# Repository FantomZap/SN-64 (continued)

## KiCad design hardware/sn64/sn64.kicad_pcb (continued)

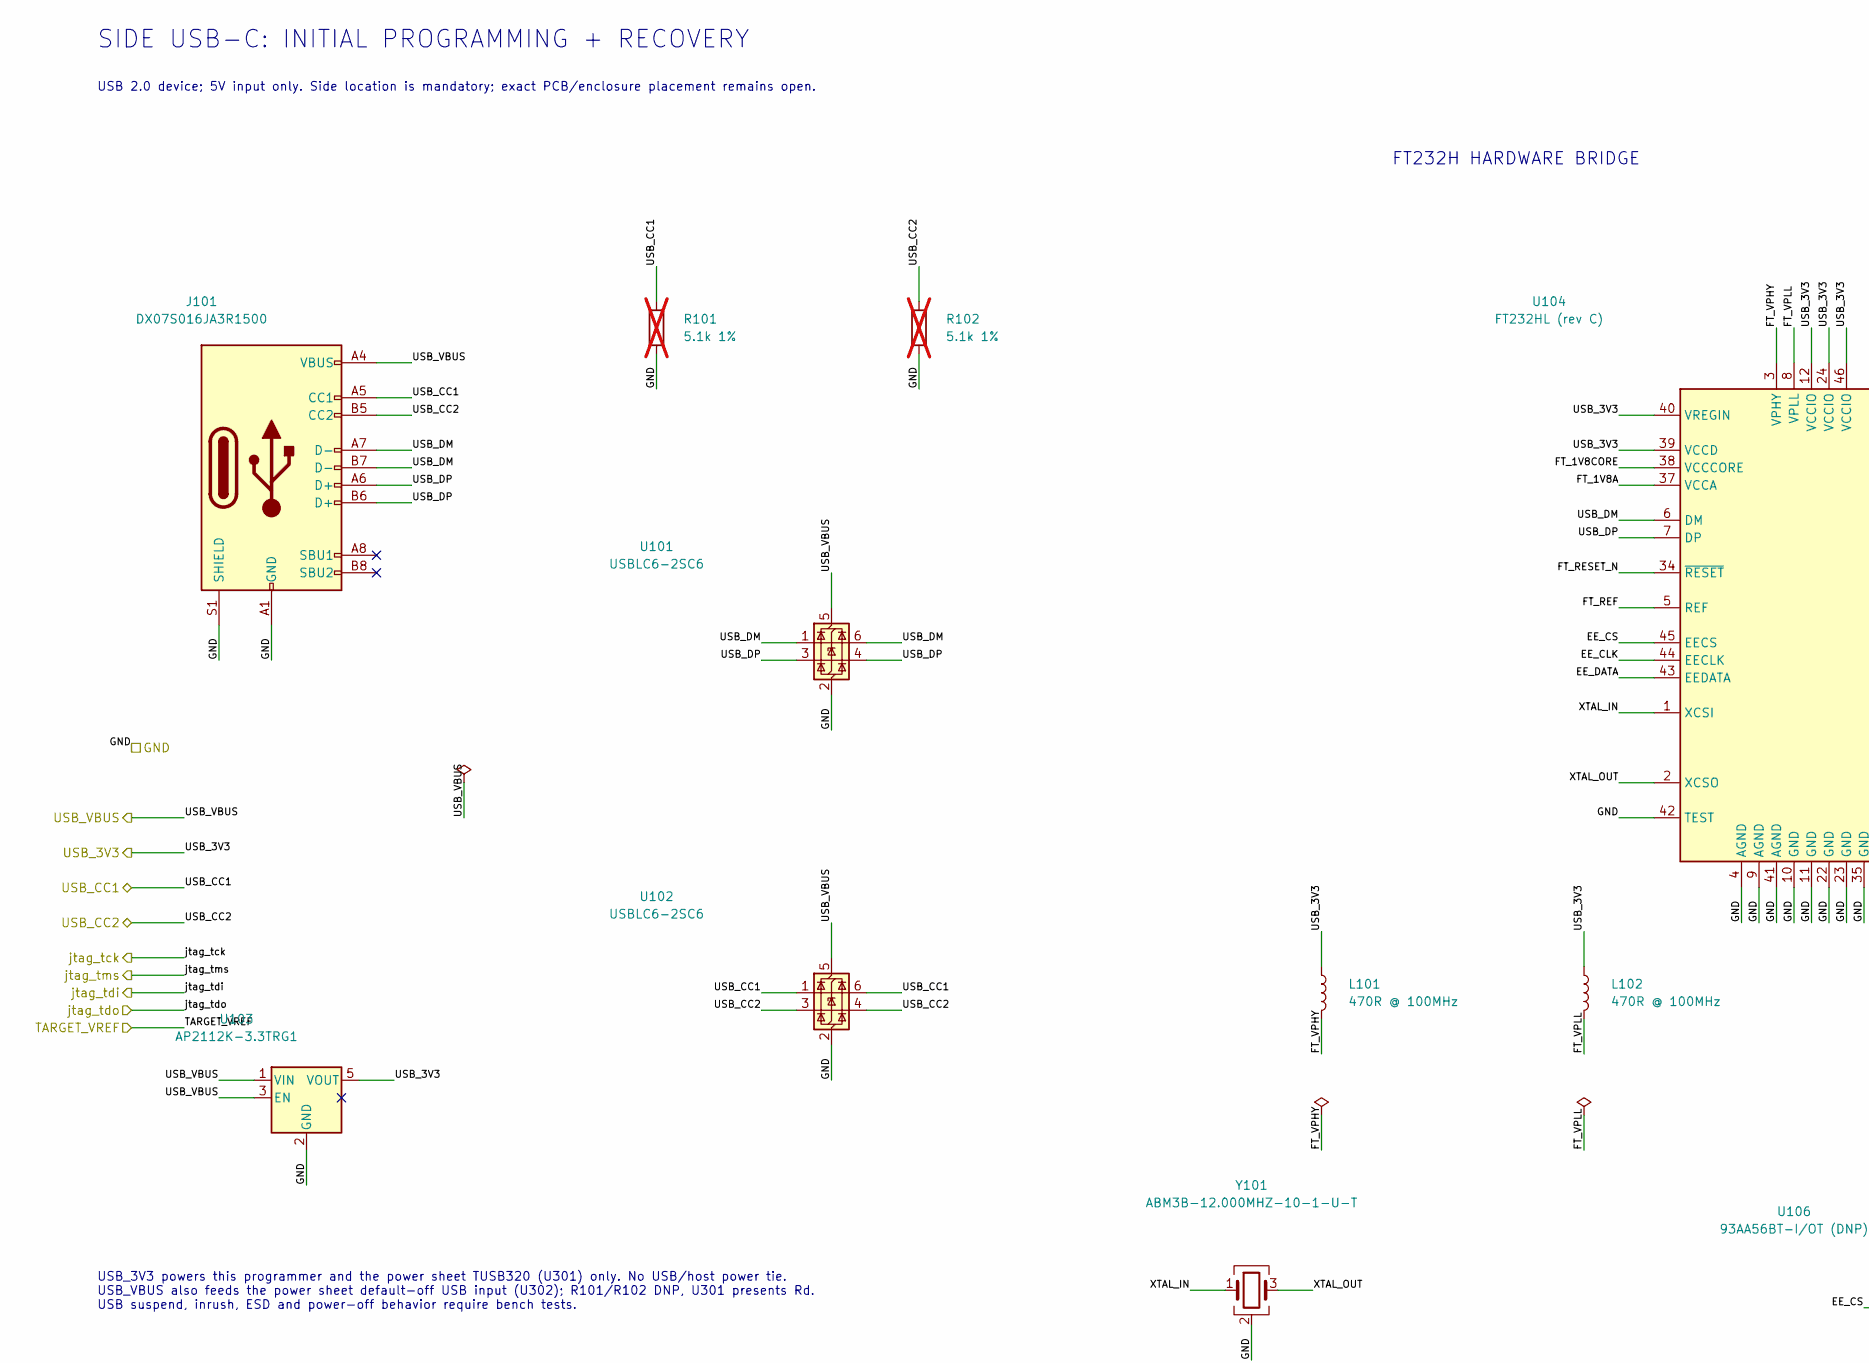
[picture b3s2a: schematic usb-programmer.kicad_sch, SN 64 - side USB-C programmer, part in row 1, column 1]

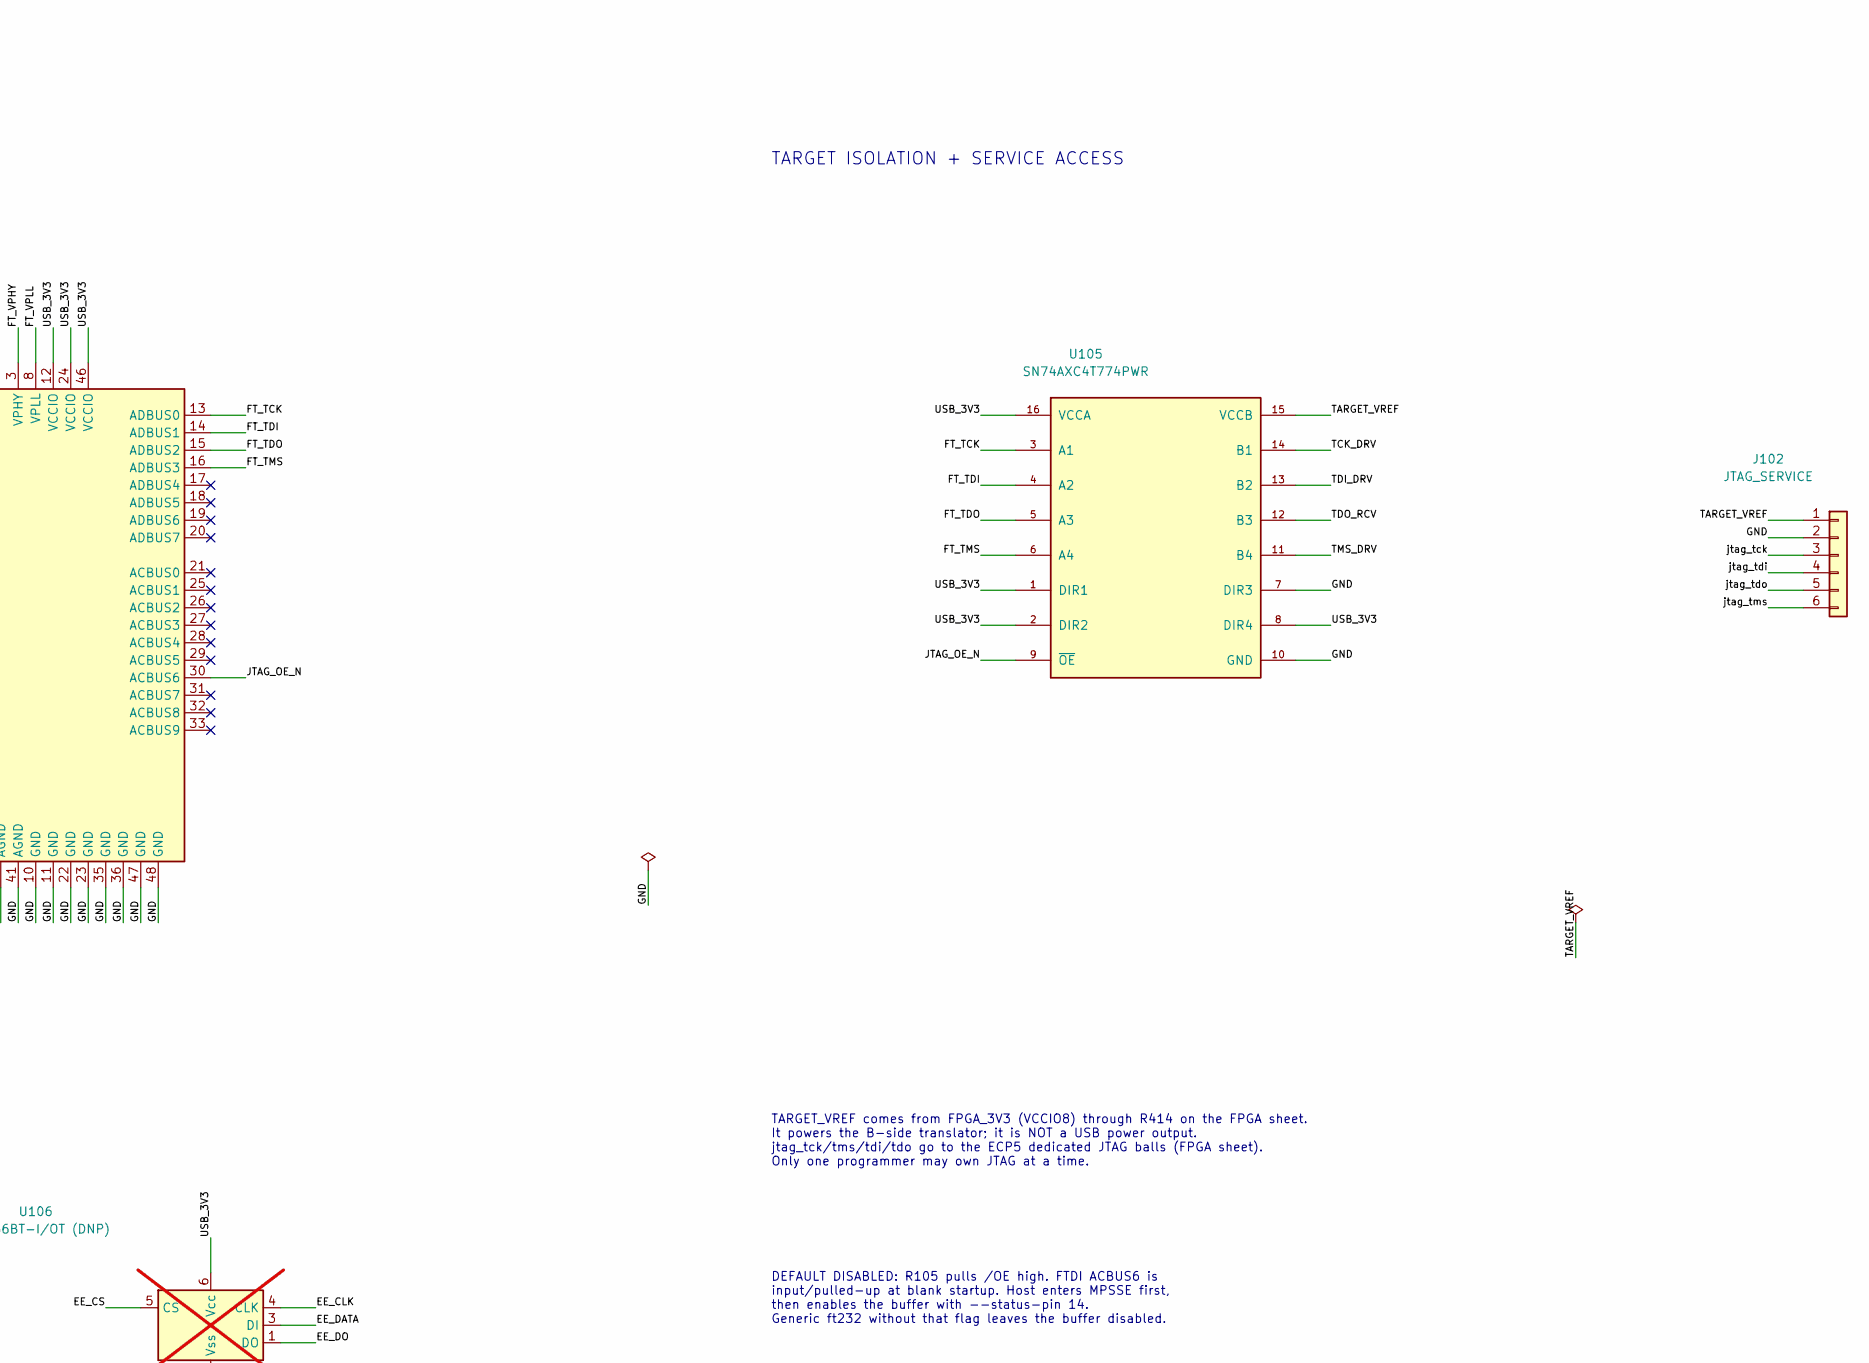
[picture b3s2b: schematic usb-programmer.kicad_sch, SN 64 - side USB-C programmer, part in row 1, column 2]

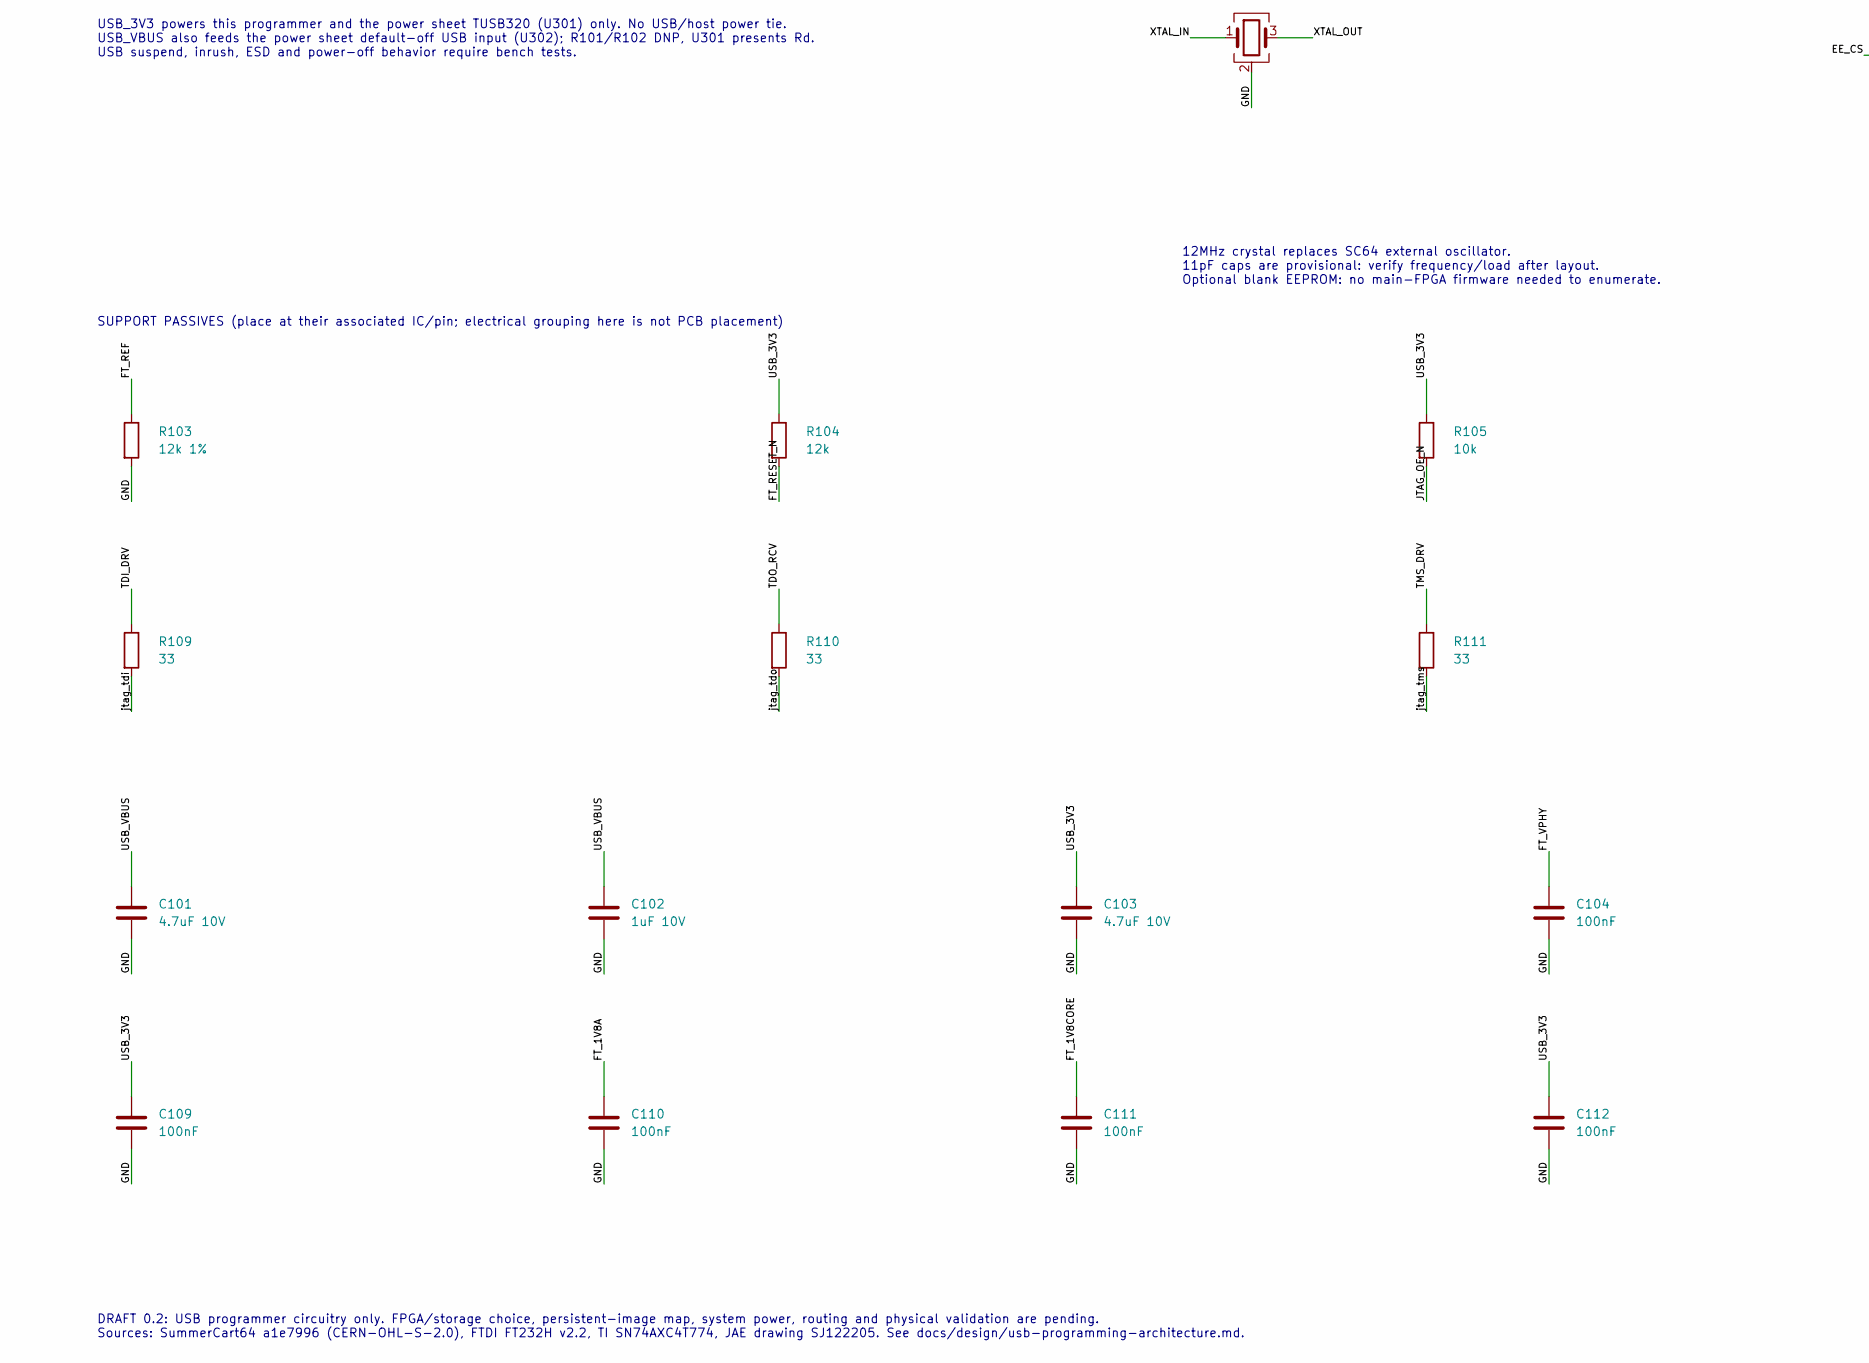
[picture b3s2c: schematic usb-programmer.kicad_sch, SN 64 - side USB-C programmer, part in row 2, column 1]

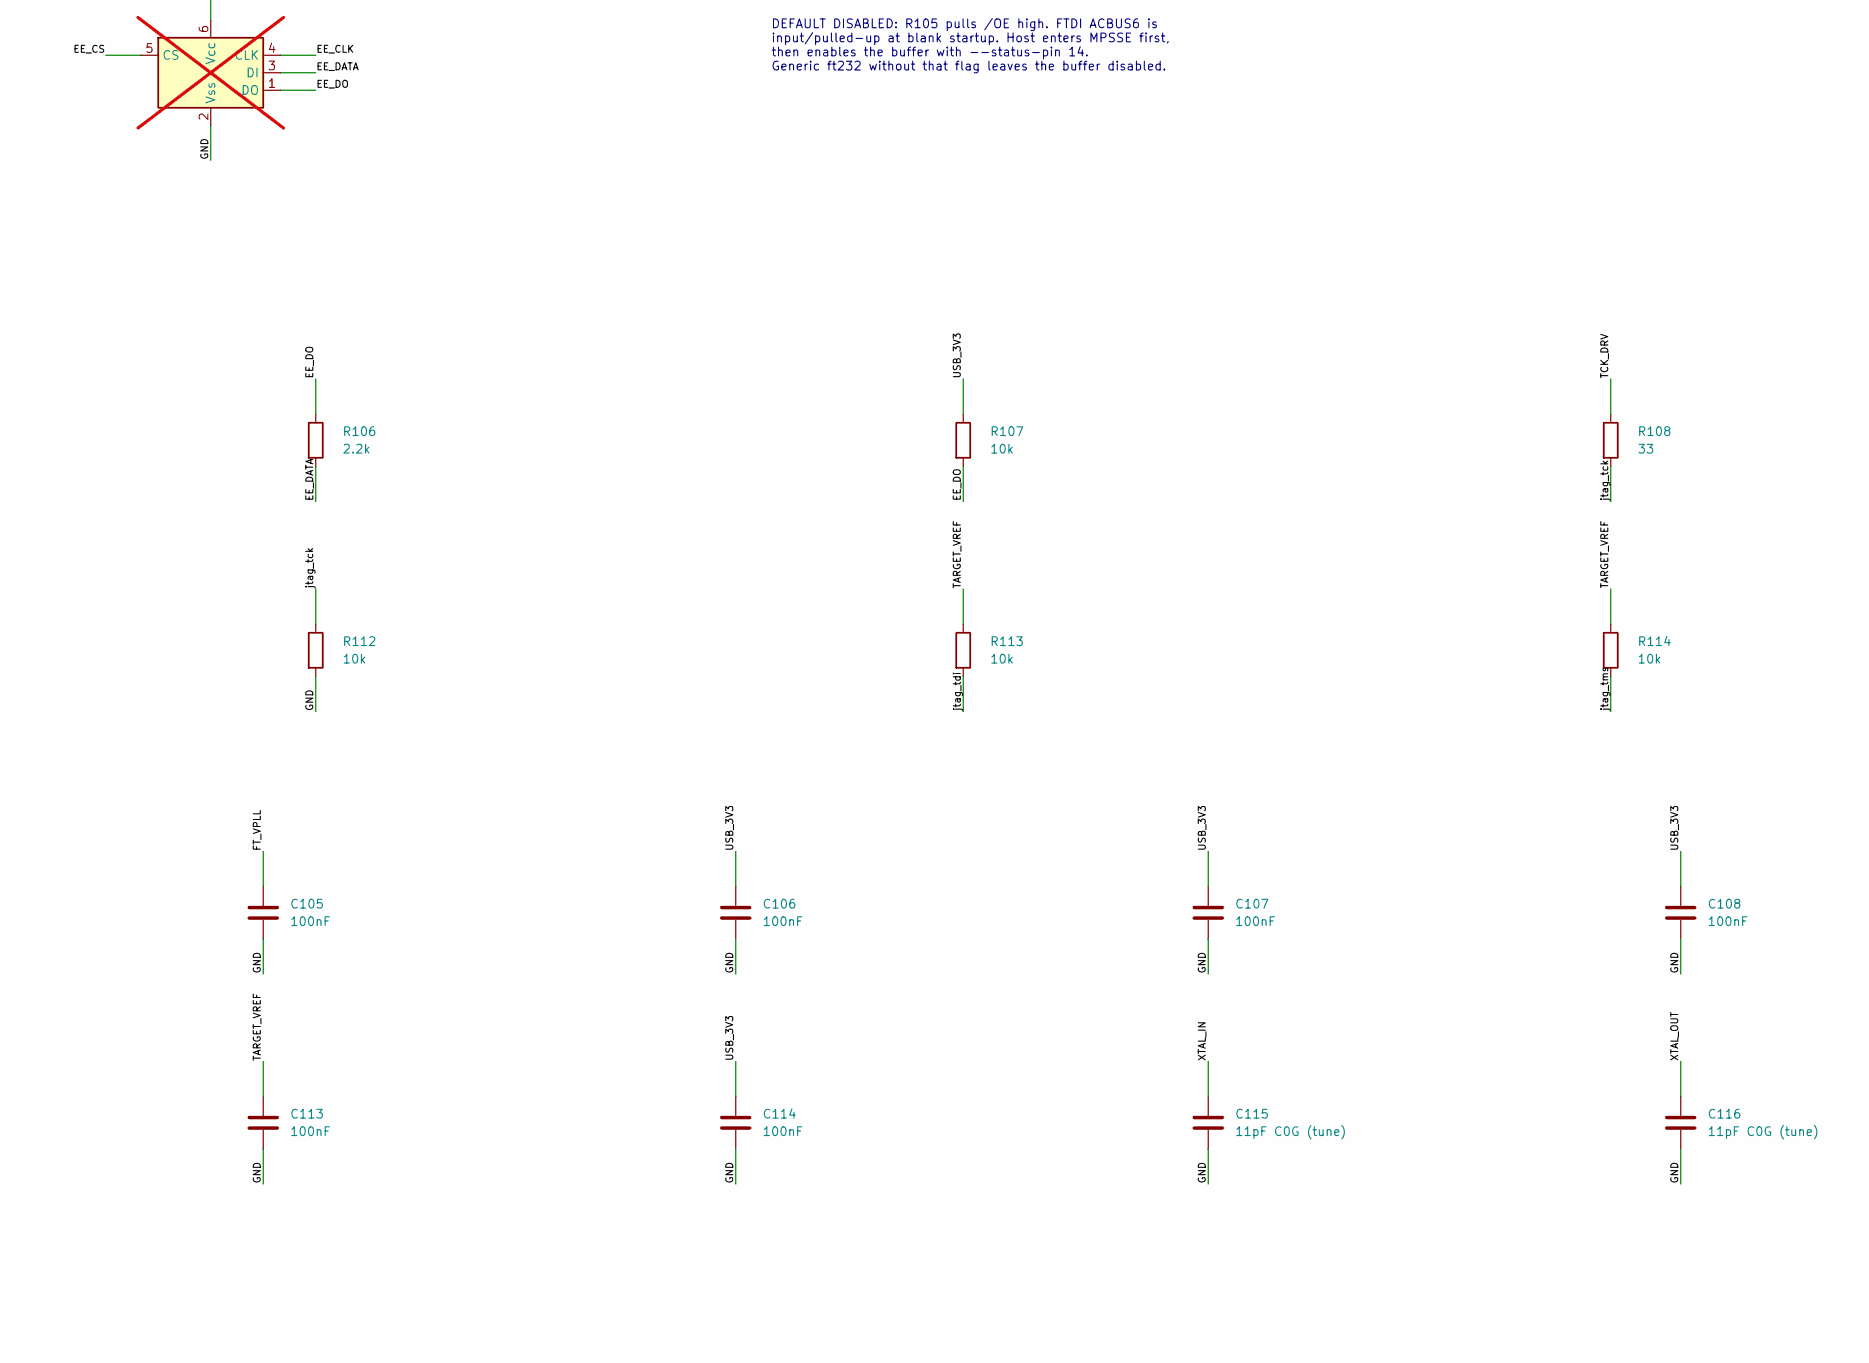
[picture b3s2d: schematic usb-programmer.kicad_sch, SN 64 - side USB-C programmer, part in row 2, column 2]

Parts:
C101, C103: 4.7uF 10V; C_0603_1608Metric
C102: 1uF 10V; C_0603_1608Metric
C104, C105, C106, C107, C108, C109, C110, C111, C112, C113, C114: 100nF; C_0603_1608Metric
C115, C116: 11pF C0G (tune); C_0603_1608Metric
J101: DX07S016JA3R1500; USB_C_JAE_DX07S016JA3R1500
J102: JTAG_SERVICE; PinHeader_1x06_P2.54mm_Vertical
L101, L102: 470R @ 100MHz; L_0603_1608Metric
R101, R102: 5.1k 1%; R_0603_1608Metric; not fitted
R103: 12k 1%; R_0603_1608Metric
R104: 12k; R_0603_1608Metric
R105, R107, R112, R113, R114: 10k; R_0603_1608Metric
R106: 2.2k; R_0603_1608Metric
R108, R109, R110, R111: 33; R_0603_1608Metric
U101, U102: USBLC6-2SC6; SOT-23-6
U103: AP2112K-3.3TRG1; SOT-23-5
U104: FT232HL (rev C); LQFP-48_7x7mm_P0.5mm
U105: SN74AXC4T774PWR; TSSOP-16_4.4x5mm_P0.65mm
U106: 93AA56BT-I/OT (DNP); SOT-23-6; not fitted
Y101: ABM3B-12.000MHZ-10-1-U-T; Crystal_SMD_Abracon_ABM3B-4Pin_5.0x3.2mm

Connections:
/GND: C101.2, C102.2, C103.2, C104.2, C105.2, C106.2, C107.2, C108.2, C109.2, C110.2, C111.2, C112.2, C113.2, C114.2, C115.2, C116.2, J101.A1 (GND), J101.A12 (GND), J101.B1 (GND), J101.B12 (GND), J101.S1 (SHIELD), J102.2, R101.2, R102.2, R103.2, R112.2, U101.2 (GND), U102.2 (GND), U103.2 (GND), U104.4 (AGND), U104.9 (AGND), U104.10 (GND), U104.11 (GND), U104.22 (GND), U104.23 (GND), U104.35 (GND), U104.36 (GND), U104.41 (AGND), U104.42 (TEST), U104.47 (GND), U104.48 (GND), U105.7 (DIR3), U105.10 (GND), U106.2 (Vss), Y101.2 (G), Y101.4 (G); also elsewhere on the board
/TARGET_VREF: C113.1, J102.1, R113.1, R114.1, U105.15 (VCCB); also elsewhere on the board
/USB-C programmer/EE_CLK: U104.44 (EECLK), U106.4 (CLK)
/USB-C programmer/EE_CS: U104.45 (EECS), U106.5 (CS)
/USB-C programmer/EE_DATA: R106.2, U104.43 (EEDATA), U106.3 (DI)
/USB-C programmer/EE_DO: R106.1, R107.2, U106.1 (DO)
/USB-C programmer/FT_1V8A: C110.1, U104.37 (VCCA)
/USB-C programmer/FT_1V8CORE: C111.1, U104.38 (VCCCORE)
/USB-C programmer/FT_REF: R103.1, U104.5 (REF)
/USB-C programmer/FT_RESET_N: R104.2, U104.34 (~RESET)
/USB-C programmer/FT_TCK: U104.13 (ADBUS0), U105.3 (A1)
/USB-C programmer/FT_TDI: U104.14 (ADBUS1), U105.4 (A2)
/USB-C programmer/FT_TDO: U104.15 (ADBUS2), U105.5 (A3)
/USB-C programmer/FT_TMS: U104.16 (ADBUS3), U105.6 (A4)
/USB-C programmer/FT_VPHY: C104.1, L101.2, U104.3 (VPHY)
/USB-C programmer/FT_VPLL: C105.1, L102.2, U104.8 (VPLL)
/USB-C programmer/JTAG_OE_N: R105.2, U104.30 (ACBUS6), U105.9 (~OE)
/USB-C programmer/TCK_DRV: R108.1, U105.14 (B1)
/USB-C programmer/TDI_DRV: R109.1, U105.13 (B2)
/USB-C programmer/TDO_RCV: R110.1, U105.12 (B3)
/USB-C programmer/TMS_DRV: R111.1, U105.11 (B4)
/USB-C programmer/USB_DM: J101.A7 (D-), J101.B7 (D-), U101.1 (I/O1), U101.6 (I/O1), U104.6 (DM)
/USB-C programmer/USB_DP: J101.A6 (D+), J101.B6 (D+), U101.3 (I/O2), U101.4 (I/O2), U104.7 (DP)
/USB-C programmer/XTAL_IN: C115.1, U104.1 (XCSI), Y101.1
/USB-C programmer/XTAL_OUT: C116.1, U104.2 (XCSO), Y101.3
/USB_3V3: C103.1, C106.1, C107.1, C108.1, C109.1, C112.1, C114.1, L101.1, L102.1, R104.1, R105.1, R107.1, U103.5 (VOUT), U104.12 (VCCIO), U104.24 (VCCIO), U104.39 (VCCD), U104.40 (VREGIN), U104.46 (VCCIO), U105.1 (DIR1), U105.2 (DIR2), U105.8 (DIR4), U105.16 (VCCA), U106.6 (Vсс); also elsewhere on the board
/USB_CC1: J101.A5 (CC1), R101.1, U102.1 (I/O1), U102.6 (I/O1); also elsewhere on the board
/USB_CC2: J101.B5 (CC2), R102.1, U102.3 (I/O2), U102.4 (I/O2); also elsewhere on the board
/USB_VBUS: C101.1, C102.1, J101.A4 (VBUS), J101.A9 (VBUS), J101.B4 (VBUS), J101.B9 (VBUS), U101.5 (VBUS), U102.5 (VBUS), U103.1 (VIN), U103.3 (EN); also elsewhere on the board
/jtag_tck: J102.3, R108.2, R112.1; also elsewhere on the board
/jtag_tdi: J102.4, R109.2, R113.2; also elsewhere on the board
/jtag_tdo: J102.5, R110.2; also elsewhere on the board
/jtag_tms: J102.6, R111.2, R114.2; also elsewhere on the board

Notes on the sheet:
SIDE USB-C: INITIAL PROGRAMMING + RECOVERY
USB 2.0 device; 5V input only. Side location is mandatory; exact PCB/enclosure placement remains open.
FT232H HARDWARE BRIDGE
TARGET ISOLATION + SERVICE ACCESS
TARGET_VREF comes from FPGA_3V3 (VCCIO8) through R414 on the FPGA sheet. It powers the B-side translator; it is NOT a USB power output. jtag_tck/tms/tdi/tdo go to the ECP5 dedicated JTAG balls (FPGA sheet). Only one programmer may own JTAG at a time.
DEFAULT DISABLED: R105 pulls /OE high. FTDI ACBUS6 is input/pulled-up at blank startup. Host enters MPSSE first, then enables the buffer with --status-pin 14. Generic ft232 without that flag leaves the buffer disabled.
USB_3V3 powers this programmer and the power sheet TUSB320 (U301) only. No USB/host power tie. USB_VBUS also feeds the power sheet default-off USB input (U302); R101/R102 DNP, U301 presents Rd. USB suspend, inrush, ESD and power-off behavior require bench tests.
12MHz crystal replaces SC64 external oscillator. 11pF caps are provisional: verify frequency/load after layout. Optional blank EEPROM: no main-FPGA firmware needed to enumerate.
SUPPORT PASSIVES (place at their associated IC/pin; electrical grouping here is not PCB placement)
DRAFT 0.2: USB programmer circuitry only. FPGA/storage choice, persistent-image map, system power, routing and physical validation are pending. Sources: SummerCart64 a1e7996 (CERN-OHL-S-2.0), FTDI FT232H v2.2, TI SN74AXC4T774, JAE drawing SJ122205. See docs/design/usb-programming-architecture.md.

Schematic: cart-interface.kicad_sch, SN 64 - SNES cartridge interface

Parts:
C201, C202, C203, C204, C205, C206, C207, C208, C209, C210, C211, C212, C213, C214, C215, C216, C217, C218, C219, C220, C221, C222, C223, C224, C225, C226, C227, C228, C229, C230, C231: 100nF; C_0603_1608Metric
C232, C233: 10uF 10V; C_0805_2012Metric
Q201: 2N7002; SOT-23
R201, R202: 2.2k; R_0603_1608Metric
R203, R204: 1k; R_0603_1608Metric
R205, R218, R219: 100k; R_0603_1608Metric
R206, R207, R208: 4.7k; R_0603_1608Metric
R209, R210, R211, R212, R213, R216, R217, R220, R221: 10k; R_0603_1608Metric
R214, R215: 33; R_0603_1608Metric
RN201, RN202, RN203, RN204, RN205, RN206, RN207, RN208, RN209, RN210, RN211, RN212, RN213: 33 (4x0603, tune); R_Array_Convex_4x0603
TP201: AUDIO_L; TestPoint_Pad_D1.0mm
TP202: AUDIO_R; TestPoint_Pad_D1.0mm
U201, U202, U203, U204, U205, U206, U207: SN74LVC4245APWR; TSSOP-24_4.4x7.8mm_P0.65mm
U209: SN74LVC244APWR; TSSOP-20_4.4x6.5mm_P0.65mm
U210, U211, U212: SN74LVC1G07DBVR; SOT-23-5
U213, U214: SN74LVC1G06DBVR; SOT-23-5
U215, U216: SN74LVC1T45DBVR; SOT-23-6; LCSC C7843

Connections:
/GND: C201.2, C202.2, C203.2, C204.2, C205.2, C206.2, C207.2, C208.2, C209.2, C210.2, C211.2, C212.2, C213.2, C214.2, C215.2, C216.2, C217.2, C218.2, C219.2, C220.2, C221.2, C222.2, C223.2, C224.2, C225.2, C226.2, C227.2, C228.2, C229.2, C230.2, C231.2, C232.2, C233.2, Q201.2 (S), R209.2, R210.2, R216.2, R217.2, R218.2, R219.2, R220.2, R221.2, U201.2 (DIR), U201.11 (GND), U201.12 (GND), U201.13 (GND), U202.2 (DIR), U202.11 (GND), U202.12 (GND), U202.13 (GND), U203.2 (DIR), U203.11 (GND), U203.12 (GND), U203.13 (GND), U204.2 (DIR), U204.11 (GND), U204.12 (GND), U204.13 (GND), U205.2 (DIR), U205.11 (GND), U205.12 (GND), U205.13 (GND), U206.2 (DIR), U206.11 (GND), U206.12 (GND), U206.13 (GND), U206.14 (B8), U206.15 (B7), U206.16 (B6), U206.17 (B5), U206.18 (B4), U207.11 (GND), U207.12 (GND), U207.13 (GND), U209.1 (~1OE), U209.8 (1A4), U209.10 (GND), U209.11 (2A1), U209.13 (2A2), U209.15 (2A3), U209.17 (2A4), U209.19 (~2OE), U210.3 (GND), U211.3 (GND), U212.3 (GND), U213.3 (GND), U214.3 (GND), U215.2 (GND), U216.2 (GND); also elsewhere on the board
/INTERFACE_3V3: C202.1, C203.1, C205.1, C206.1, C208.1, C209.1, C211.1, C212.1, C214.1, C215.1, C217.1, C218.1, C220.1, C221.1, C222.1, C223.1, C224.1, C225.1, C226.1, C227.1, C228.1, C230.1, C233.1, R206.1, R207.1, R208.1, U201.23 (VCCB), U201.24 (VCCB), U202.23 (VCCB), U202.24 (VCCB), U203.23 (VCCB), U203.24 (VCCB), U204.23 (VCCB), U204.24 (VCCB), U205.23 (VCCB), U205.24 (VCCB), U206.23 (VCCB), U206.24 (VCCB), U207.23 (VCCB), U207.24 (VCCB), U209.20 (VCC), U210.5 (VCC), U211.5 (VCC), U212.5 (VCC), U213.5 (VCC), U214.5 (VCC), U215.1 (VCCA), U216.1 (VCCA); also elsewhere on the board
/SNES cartridge interface/CIC_OE_N_5V: R202.2, U206.22 (~OE), U211.4
/SNES cartridge interface/CTL_OE_N_5V: R201.2, U201.22 (~OE), U202.22 (~OE), U203.22 (~OE), U204.22 (~OE), U205.22 (~OE), U210.4
/SNES cartridge interface/DATA_DIR_5V: R204.2, U207.2 (DIR), U213.4
/SNES cartridge interface/DATA_OE_N_5V: R203.2, U207.22 (~OE), U212.4
/SNES cartridge interface/RESET_GATE_5V: Q201.1 (G), R205.2, U214.4
/SNES cartridge interface/XA_A0: RN201.1 (R1.1), U201.3 (A1)
/SNES cartridge interface/XA_A1: RN201.2 (R2.1), U201.4 (A2)
/SNES cartridge interface/XA_A2: RN201.3 (R3.1), U201.5 (A3)
/SNES cartridge interface/XA_A3: RN201.4 (R4.1), U201.6 (A4)
/SNES cartridge interface/XA_A4: RN202.1 (R1.1), U201.7 (A5)
/SNES cartridge interface/XA_A5: RN202.2 (R2.1), U201.8 (A6)
/SNES cartridge interface/XA_A6: RN202.3 (R3.1), U201.9 (A7)
/SNES cartridge interface/XA_A7: RN202.4 (R4.1), U201.10 (A8)
/SNES cartridge interface/XA_A8: RN203.1 (R1.1), U202.3 (A1)
/SNES cartridge interface/XA_A9: RN203.2 (R2.1), U202.4 (A2)
/SNES cartridge interface/XA_A10: RN203.3 (R3.1), U202.5 (A3)
/SNES cartridge interface/XA_A11: RN203.4 (R4.1), U202.6 (A4)
/SNES cartridge interface/XA_A12: RN204.1 (R1.1), U202.7 (A5)
/SNES cartridge interface/XA_A13: RN204.2 (R2.1), U202.8 (A6)
/SNES cartridge interface/XA_A14: RN204.3 (R3.1), U202.9 (A7)
/SNES cartridge interface/XA_A15: RN204.4 (R4.1), U202.10 (A8)
/SNES cartridge interface/XA_A16: RN205.1 (R1.1), U203.3 (A1)
/SNES cartridge interface/XA_A17: RN205.2 (R2.1), U203.4 (A2)
/SNES cartridge interface/XA_A18: RN205.3 (R3.1), U203.5 (A3)
/SNES cartridge interface/XA_A19: RN205.4 (R4.1), U203.6 (A4)
/SNES cartridge interface/XA_A20: RN206.1 (R1.1), U203.7 (A5)
/SNES cartridge interface/XA_A21: RN206.2 (R2.1), U203.8 (A6)
/SNES cartridge interface/XA_A22: RN206.3 (R3.1), U203.9 (A7)
/SNES cartridge interface/XA_A23: RN206.4 (R4.1), U203.10 (A8)
/SNES cartridge interface/XA_CIC_CLK: RN211.2 (R2.1), U206.4 (A2)
/SNES cartridge interface/XA_CIC_SLAVE_RESET: RN211.3 (R3.1), U206.5 (A3)
/SNES cartridge interface/XA_D0: RN212.1 (R1.1), U207.3 (A1)
/SNES cartridge interface/XA_D1: RN212.2 (R2.1), U207.4 (A2)
/SNES cartridge interface/XA_D2: RN212.3 (R3.1), U207.5 (A3)
/SNES cartridge interface/XA_D3: RN212.4 (R4.1), U207.6 (A4)
/SNES cartridge interface/XA_D4: RN213.1 (R1.1), U207.7 (A5)
/SNES cartridge interface/XA_D5: RN213.2 (R2.1), U207.8 (A6)
/SNES cartridge interface/XA_D6: RN213.3 (R3.1), U207.9 (A7)
/SNES cartridge interface/XA_D7: RN213.4 (R4.1), U207.10 (A8)
/SNES cartridge interface/XA_PA0: RN207.1 (R1.1), U204.3 (A1)
/SNES cartridge interface/XA_PA1: RN207.2 (R2.1), U204.4 (A2)
/SNES cartridge interface/XA_PA2: RN207.3 (R3.1), U204.5 (A3)
/SNES cartridge interface/XA_PA3: RN207.4 (R4.1), U204.6 (A4)
/SNES cartridge interface/XA_PA4: RN208.1 (R1.1), U204.7 (A5)
/SNES cartridge interface/XA_PA5: RN208.2 (R2.1), U204.8 (A6)
/SNES cartridge interface/XA_PA6: RN208.3 (R3.1), U204.9 (A7)
/SNES cartridge interface/XA_PA7: RN208.4 (R4.1), U204.10 (A8)
/SNES cartridge interface/XA_PHI2: RN210.4 (R4.1), U205.10 (A8)
/SNES cartridge interface/XA_PRD_N: RN209.3 (R3.1), U205.5 (A3)
/SNES cartridge interface/XA_PWR_N: RN209.4 (R4.1), U205.6 (A4)
/SNES cartridge interface/XA_RD_N: RN209.1 (R1.1), U205.3 (A1)
/SNES cartridge interface/XA_REFRESH: RN210.3 (R3.1), U205.9 (A7)
/SNES cartridge interface/XA_ROMSEL_N: RN210.1 (R1.1), U205.7 (A5)
/SNES cartridge interface/XA_SYSTEM_CLK: RN211.1 (R1.1), U206.3 (A1)
/SNES cartridge interface/XA_WRAMSEL_N: RN210.2 (R2.1), U205.8 (A6)
/SNES cartridge interface/XA_WR_N: RN209.2 (R2.1), U205.4 (A2)
/SNES cartridge interface/XB_CIC_DATA0: R214.1, U215.4 (B)
/SNES cartridge interface/XB_CIC_DATA1: R215.1, U216.4 (B)
/SNES_5V_CART: C201.1, C204.1, C207.1, C210.1, C213.1, C216.1, C219.1, C229.1, C231.1, C232.1, R201.1, R202.1, R203.1, R204.1, R205.1, R211.1, R212.1, R213.1, U201.1 (VCCA), U202.1 (VCCA), U203.1 (VCCA), U204.1 (VCCA), U205.1 (VCCA), U206.1 (VCCA), U207.1 (VCCA), U215.6 (VCCB), U216.6 (VCCB); also elsewhere on the board
/SNES_A0: RN201.8 (R1.2); also elsewhere on the board
/SNES_A1: RN201.7 (R2.2); also elsewhere on the board
/SNES_A2: RN201.6 (R3.2); also elsewhere on the board
/SNES_A3: RN201.5 (R4.2); also elsewhere on the board
/SNES_A4: RN202.8 (R1.2); also elsewhere on the board
/SNES_A5: RN202.7 (R2.2); also elsewhere on the board
/SNES_A6: RN202.6 (R3.2); also elsewhere on the board
/SNES_A7: RN202.5 (R4.2); also elsewhere on the board
/SNES_A8: RN203.8 (R1.2); also elsewhere on the board
/SNES_A9: RN203.7 (R2.2); also elsewhere on the board
/SNES_A10: RN203.6 (R3.2); also elsewhere on the board
/SNES_A11: RN203.5 (R4.2); also elsewhere on the board
/SNES_A12: RN204.8 (R1.2); also elsewhere on the board
/SNES_A13: RN204.7 (R2.2); also elsewhere on the board
/SNES_A14: RN204.6 (R3.2); also elsewhere on the board
/SNES_A15: RN204.5 (R4.2); also elsewhere on the board
/SNES_A16: RN205.8 (R1.2); also elsewhere on the board
/SNES_A17: RN205.7 (R2.2); also elsewhere on the board
/SNES_A18: RN205.6 (R3.2); also elsewhere on the board
/SNES_A19: RN205.5 (R4.2); also elsewhere on the board
/SNES_A20: RN206.8 (R1.2); also elsewhere on the board
/SNES_A21: RN206.7 (R2.2); also elsewhere on the board
/SNES_A22: RN206.6 (R3.2); also elsewhere on the board
/SNES_A23: RN206.5 (R4.2); also elsewhere on the board
/SNES_AUDIO_L_IN: TP201.1; also elsewhere on the board
/SNES_AUDIO_R_IN: TP202.1; also elsewhere on the board
/SNES_CIC_CLK: RN211.7 (R2.2); also elsewhere on the board
/SNES_CIC_DATA0: R214.2, R216.1; also elsewhere on the board
/SNES_CIC_DATA1: R215.2, R217.1; also elsewhere on the board
/SNES_CIC_SLAVE_RESET: RN211.6 (R3.2); also elsewhere on the board
/SNES_D0: RN212.8 (R1.2); also elsewhere on the board
/SNES_D1: RN212.7 (R2.2); also elsewhere on the board
/SNES_D2: RN212.6 (R3.2); also elsewhere on the board
/SNES_D3: RN212.5 (R4.2); also elsewhere on the board
/SNES_D4: RN213.8 (R1.2); also elsewhere on the board
/SNES_D5: RN213.7 (R2.2); also elsewhere on the board
/SNES_D6: RN213.6 (R3.2); also elsewhere on the board
/SNES_D7: RN213.5 (R4.2); also elsewhere on the board
/SNES_EXPAND: R213.2, U209.6 (1A3); also elsewhere on the board
/SNES_IRQ_N: R211.2, U209.2 (1A1); also elsewhere on the board
/SNES_PA0: RN207.8 (R1.2); also elsewhere on the board
/SNES_PA1: RN207.7 (R2.2); also elsewhere on the board
/SNES_PA2: RN207.6 (R3.2); also elsewhere on the board
/SNES_PA3: RN207.5 (R4.2); also elsewhere on the board
/SNES_PA4: RN208.8 (R1.2); also elsewhere on the board
/SNES_PA5: RN208.7 (R2.2); also elsewhere on the board
/SNES_PA6: RN208.6 (R3.2); also elsewhere on the board
/SNES_PA7: RN208.5 (R4.2); also elsewhere on the board
/SNES_PHI2: RN210.5 (R4.2); also elsewhere on the board
/SNES_PRD_N: RN209.6 (R3.2); also elsewhere on the board
/SNES_PWR_N: RN209.5 (R4.2); also elsewhere on the board
/SNES_RD_N: RN209.8 (R1.2); also elsewhere on the board
/SNES_REFRESH: RN210.6 (R3.2); also elsewhere on the board
/SNES_RESET_N: Q201.3 (D), R212.2, U209.4 (1A2); also elsewhere on the board
/SNES_ROMSEL_N: RN210.8 (R1.2); also elsewhere on the board
/SNES_SYSTEM_CLK: RN211.8 (R1.2); also elsewhere on the board
/SNES_WRAMSEL_N: RN210.7 (R2.2); also elsewhere on the board
/SNES_WR_N: RN209.7 (R2.2); also elsewhere on the board
/cart_address0: U201.21 (B1); also elsewhere on the board
/cart_address1: U201.20 (B2); also elsewhere on the board
/cart_address2: U201.19 (B3); also elsewhere on the board
/cart_address3: U201.18 (B4); also elsewhere on the board
/cart_address4: U201.17 (B5); also elsewhere on the board
/cart_address5: U201.16 (B6); also elsewhere on the board
/cart_address6: U201.15 (B7); also elsewhere on the board
/cart_address7: U201.14 (B8); also elsewhere on the board
/cart_address8: U202.21 (B1); also elsewhere on the board
/cart_address9: U202.20 (B2); also elsewhere on the board
/cart_address10: U202.19 (B3); also elsewhere on the board
/cart_address11: U202.18 (B4); also elsewhere on the board
/cart_address12: U202.17 (B5); also elsewhere on the board
/cart_address13: U202.16 (B6); also elsewhere on the board
/cart_address14: U202.15 (B7); also elsewhere on the board
/cart_address15: U202.14 (B8); also elsewhere on the board
/cart_address16: U203.21 (B1); also elsewhere on the board
/cart_address17: U203.20 (B2); also elsewhere on the board
/cart_address18: U203.19 (B3); also elsewhere on the board
/cart_address19: U203.18 (B4); also elsewhere on the board
/cart_address20: U203.17 (B5); also elsewhere on the board
/cart_address21: U203.16 (B6); also elsewhere on the board
/cart_address22: U203.15 (B7); also elsewhere on the board
/cart_address23: U203.14 (B8); also elsewhere on the board
/cart_data0: U207.21 (B1); also elsewhere on the board
/cart_data1: U207.20 (B2); also elsewhere on the board
/cart_data2: U207.19 (B3); also elsewhere on the board
/cart_data3: U207.18 (B4); also elsewhere on the board
/cart_data4: U207.17 (B5); also elsewhere on the board
/cart_data5: U207.16 (B6); also elsewhere on the board
/cart_data6: U207.15 (B7); also elsewhere on the board
/cart_data7: U207.14 (B8); also elsewhere on the board
/cart_irq_n: U209.18 (1Y1); also elsewhere on the board
/cart_pa0: U204.21 (B1); also elsewhere on the board
/cart_pa1: U204.20 (B2); also elsewhere on the board
/cart_pa2: U204.19 (B3); also elsewhere on the board
/cart_pa3: U204.18 (B4); also elsewhere on the board
/cart_pa4: U204.17 (B5); also elsewhere on the board
/cart_pa5: U204.16 (B6); also elsewhere on the board
/cart_pa6: U204.15 (B7); also elsewhere on the board
/cart_pa7: U204.14 (B8); also elsewhere on the board
/cart_phi2: U205.14 (B8); also elsewhere on the board
/cart_prd_n: U205.19 (B3); also elsewhere on the board
/cart_pwr_n: U205.18 (B4); also elsewhere on the board
/cart_rd_n: U205.21 (B1); also elsewhere on the board
/cart_refresh: U205.15 (B7); also elsewhere on the board
/cart_reset_n_sense: U209.16 (1Y2); also elsewhere on the board
/cart_reset_pull_n: R210.1, U214.2; also elsewhere on the board
/cart_romsel_n: U205.17 (B5); also elsewhere on the board
/cart_sysclk: U206.21 (B1); also elsewhere on the board
/cart_wr_n: U205.20 (B2); also elsewhere on the board
/cart_wramsel_n: U205.16 (B6); also elsewhere on the board
/cic_clk: U206.20 (B2); also elsewhere on the board
/cic_data0: R218.1, U215.3 (A); also elsewhere on the board
/cic_data0_dir: R220.1, U215.5 (DIR); also elsewhere on the board
/cic_data1: R219.1, U216.3 (A); also elsewhere on the board
/cic_data1_dir: R221.1, U216.5 (DIR); also elsewhere on the board
/cic_oe_n: R207.2, U211.2; also elsewhere on the board
/cic_slave_reset: U206.19 (B3); also elsewhere on the board
/ctl_oe_n: R206.2, U210.2; also elsewhere on the board
/data_dir: R209.1, U213.2; also elsewhere on the board
/data_oe_n: R208.2, U212.2; also elsewhere on the board
/expand_sense: U209.14 (1Y3); also elsewhere on the board

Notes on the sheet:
SNES CARTRIDGE-SIDE TRANSLATION AND PROTECTION
SN74LVC4245A: A port = 5 V cartridge (VCCA = SNES_5V_CART), B port = 3.3 V FPGA (VCCB = INTERFACE_3V3). DIR/OE are referenced to VCCA (TI SCAS375K). DIR=L: B->A (FPGA drives socket); DIR=H: A->B; OE=H: isolation.
U201-U206: console outputs, DIR strapped to GND (fixed FPGA->cartridge). U201-U205 share CTL_OE_N_5V (bridge ctl_oe_n); U206 (SYSTEM_CLK + CIC_CLK + CIC_SLAVE_RESET only) has its own CIC_OE_N_5V (sn64_top snes_cic_oe_n, enabled from the sequencer IFACE state). U207: D0-D7, DIR and OE both FPGA-cont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
CARTRIDGE OUTPUT DAMPING: 33 R arrays at the translator A pins (source-series). Values are provisional; tune after SI measurement.
SENSE + RELEASE PATHS
U209 SN74LVC244A at 3.3 V: 5.5 V-tolerant inputs with Ioff; receives /IRQ, /RESET, EXPAND (CIC data pins use U215/U216). U210-U212 74LVC1G07 / U213 74LVC1G06: 3.3 V open-drain outputs (5.5 V tolerant, Ioff) pulled to SNES_5V_CART. No 5 V pull-up reaches an FPGA pin. Interface rail off or FPGA uncon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
/OE and DIR edge timing: the bridge releases the data octet one 46.56 ns clock before turnaround. R203/R204 = 1k keep the passive rising edge short (about 10 pF load: tau ~10 ns); R201/R202 2.2k drive five/one /OE inputs where only permit-loss timing matters. Verify on hardware.
PULL/BIAS: /IRQ, /RESET, EXPAND 10k to cartridge 5 V (OpenSFC keeps pull-ups on IRQ/EXPAND); CIC_DATA0/1 10k pull-downs (R216/R217). Values provisional.
CIC DATA PINS - PER-PIN DIRECTION CONTROL (J2.55 CIC_DATA0 via U215, J2.24 CIC_DATA1 via U216)
SN74LVC1T45 (TI SCES515N): A = FPGA side (VCCA = INTERFACE_3V3), B = cartridge side (VCCB = SNES_5V_CART). No shared enable. DIR is referenced to VCCA and driven directly by its own FPGA pin cic_dataN_dir: H = A->B (FPGA drives the cartridge), L = B->A (listen). FPGA rule (no OE pin, SCES515N 8.2.2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
DECOUPLING: one 100 nF per supply pin (place at the pin) plus one 10 uF bulk per rail.
AUDIO: AUDIO_L_IN / AUDIO_R_IN pass untouched (no digital translation); test points only.
HIERARCHICAL PORTS - CARTRIDGE SIDE (root J2 net labels)
PENDING PORTS - FPGA SIDE (bridge port names) + DEFAULT-OFF RAILS FROM FUTURE POWER SHEET
DRAFT 0.3.1-cart: schematic circuit candidate only. No PCB, SI simulation, power sequencing test, ESD part or cartridge test has been performed. SNES_5V_CART and INTERFACE_3V3 are hierarchical inputs from the power sheet; #FLG201/#FLG202 are kept because the power-sheet switch outputs are passive p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
